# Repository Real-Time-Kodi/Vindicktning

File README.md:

# Vindicktning
This board is designed to fit within the case of the Ikea Vindriktning and
replicate its functionality while replacing the main MCU with an ESP8266 for
home automation use. It also adds multiple i2c headers for adding other air 
quality sensors.  

# Harvesting Components
This step is relatively straightforward, I recommend using a soldering 
hotplate and a pinecil or similar small, temperature controlled iron.
The first step is to harvest the parts you'll need from the Vindriktning
 board. Remove all of the components circled in red. The easiest way to do this
 is to scrape the LEDs off of the underside of the board and put it on the
hotplate, removing each component with tweezers once the board is good and hot.  
You'll need both of the connectors, the electrolytic cap, and the diode.

# Parts List
- [Usb Type C Connector](https://www.mouser.com/ProductDetail/640-USB4120-03-C)
- 7x 0805 0.1uf Capacitors
- 3x WS2812b LEDs
- 1x 0805 10k Resistor(optional for buzzer)
- 1x [MMBT2222](https://www.mouser.com/ProductDetail/241-MMBT2222AR100001) SOT Transistor or equivalent(optional for buzzer)
- 1x Standard buzzer(optional)
- Fine wire(Optional for USB data hookup)
- Wemos D1 Mini  

I have a few kits available on my [tindie page](https://www.tindie.com/products/realtimekodi/vindriktning-air-quality-sensor-mod-boardesphome/#shipping).  

# Board Assembly
Using your preferred method, solder each of the components on to their 
designated pads. All of the capacitors are 0.1uf except for the electrolytic 
capacitor. Mind the polarity on both the capacitor and the diode!

I recommend using the hotplate for all of the surface mount components and
verifying that you get 5v at this point before proceeding to the next steps.
Don't forget to solder the LEDs on the back.

The other board is easy to get wrong. Make sure the port and board are
facing the correct direction or the completed assembly will not fit into the
case! Look at the pictures to be sure of orientation. The ESP module on the 
Wemos D1 should fit into the board cutout and the USB port should be accessible.
Solder the boards together with small bits of wire or header pins.

It is easiest to solder the through-hole components before mating the boards 
together, this is the point where you should install the optional buzzer and 
any i2c headers you wish to use. The headers should have been included with the 
Wemos D1 and can be cut down to size with angle cutters.

# Mating the Boards
The board containing the Wemos D1 must be facing exactly as shown. Insert it 
into the slot and solder it on BOTH SIDES, making sure that it is exactly
perpendicular to the main PCB. Test the fitment before Reassembly!

# USB Data lines for External Programming(Optional)
There are two labeled test pads on the main PCB (D+ and D-) those two pads can
be connected to the corresponding D+ and D- pins on the Wemos D1's USB to Serial chip to allow
you to program the device without opening it up. There are several different USB -> Serial chips on the
D1. Check the diagram below for specific pinout. Many modules will have the model numbers sanded off of
the CH341. Note that this is not a valid implementation of USB and the type-c cable will only be able to 
program the device when inserted right-side up.

# Reassembly
The Vindrictning top case needs to have these 2 standoffs removed. Flush 
cutters work best.

The new board can then be installed with the screws that 
came with the vindriktning. Keep an eye on the header pins that hold the 
Wemos D1 to its pcb, they need to be trimmed as flush as possible in order for 
the board to clear the fan screws.

# Programming
See the included esphome example. It initializes all of the inbuilt perpherals 
and has a function for fading the LEDs between colors based on the c02, pm2.5, 
and VOC concentrations. Program it with whichever method you usually use to 
program ESPHome devices.  
Please remember that the usb port will only connect the data pins with the type-c 
connector in the upward orientation.  

# Adding I2C Sensors
Additional sensors can be added using the I2C headers. There are three of them of them
with the following pinout: SDA | SCL | GND | VCC  
The I2C4 header on the top of the board has positive and negative swapped so that it 
can be used with [this sensor](https://www.amazon.com/gp/product/B0BHHRT1F6/): 
SDA | SCL | VCC | GND  
The voltage is 3.3 by default but it can be set to 5v by cutting the voltage selector
trace and adding a solder blob on the 5v side. The silkscreen is clearly labled.

Check [ESPHome.io](https://esphome.io/) for supported sensors and configuration
documentation.

Sensors I have used:
- SCD40 (CO2)
- BME280 (Temperature Humiditity Pressure)
- BME680
- BMP280 (Temperature Pressure)
- CCS811 (eC02 Volatile Organic Compounds)

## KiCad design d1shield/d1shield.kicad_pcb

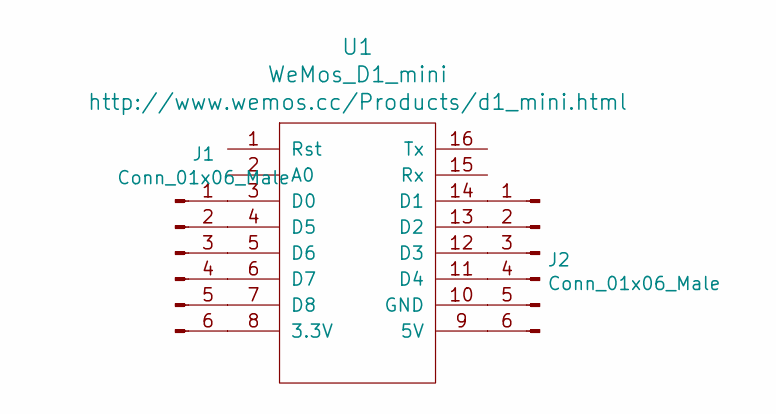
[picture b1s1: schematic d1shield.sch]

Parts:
J1, J2: Conn_01x06_Male; Edge
U1: WeMos_D1_mini; wemos-d1-mini-connectors-only

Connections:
unnamed: J1.1, U1.3 (D0)
unnamed: J1.2, U1.4 (D5)
unnamed: J1.3, U1.5 (D6)
unnamed: J1.4, U1.6 (D7)
unnamed: J1.5, U1.7 (D8)
unnamed: J1.6, U1.8 (3.3V)
unnamed: J2.1, U1.14 (D1)
unnamed: J2.2, U1.13 (D2)
unnamed: J2.3, U1.12 (D3)
unnamed: J2.4, U1.11 (D4)
unnamed: J2.5, U1.10 (GND)
unnamed: J2.6, U1.9 (5V)

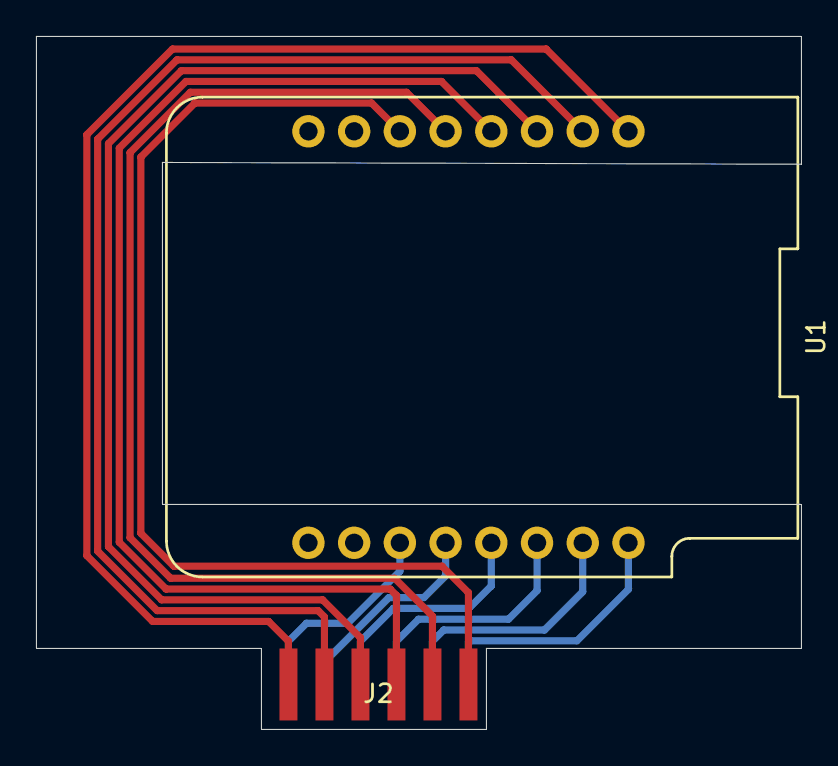
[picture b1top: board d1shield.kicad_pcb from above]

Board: 2 copper layers, 42.5 x 38.5 mm, 3 parts (1 on the bottom side), 12 nets.

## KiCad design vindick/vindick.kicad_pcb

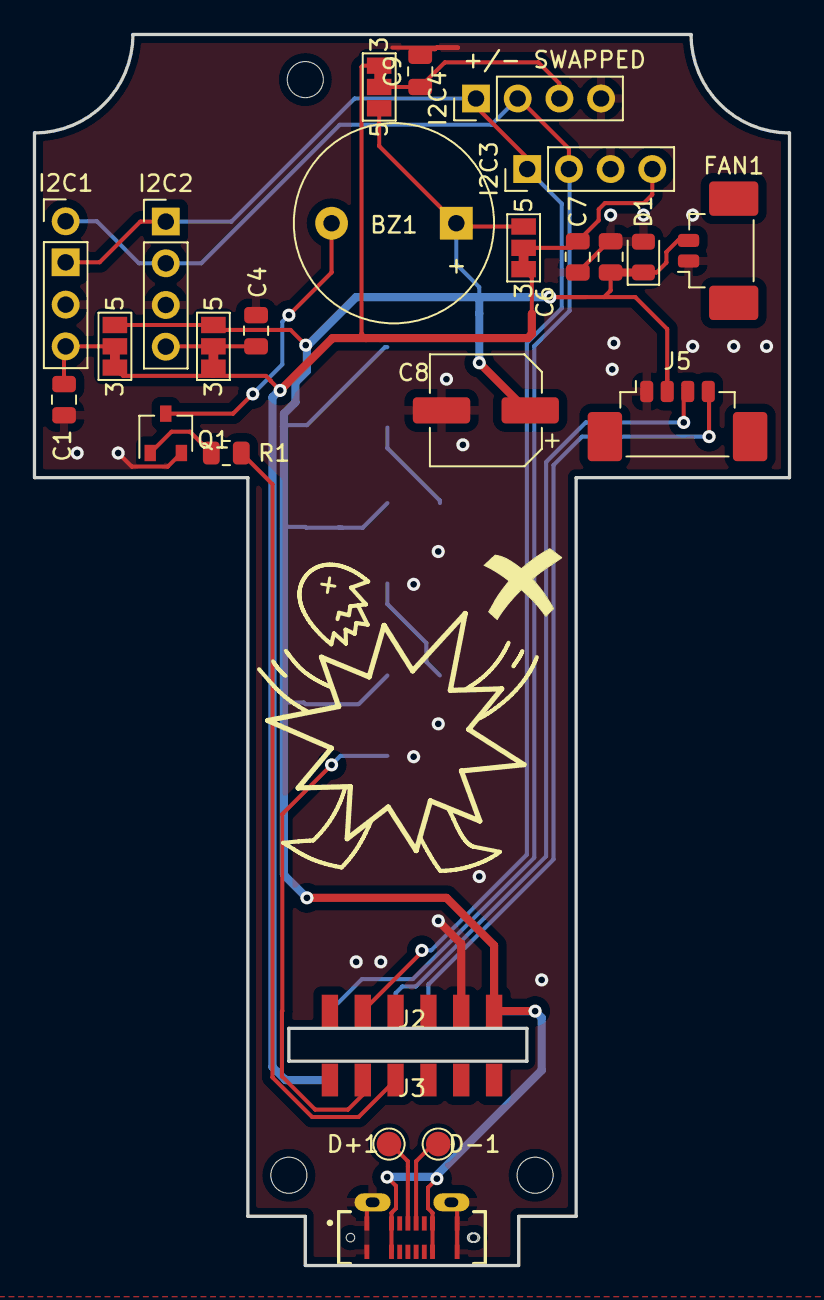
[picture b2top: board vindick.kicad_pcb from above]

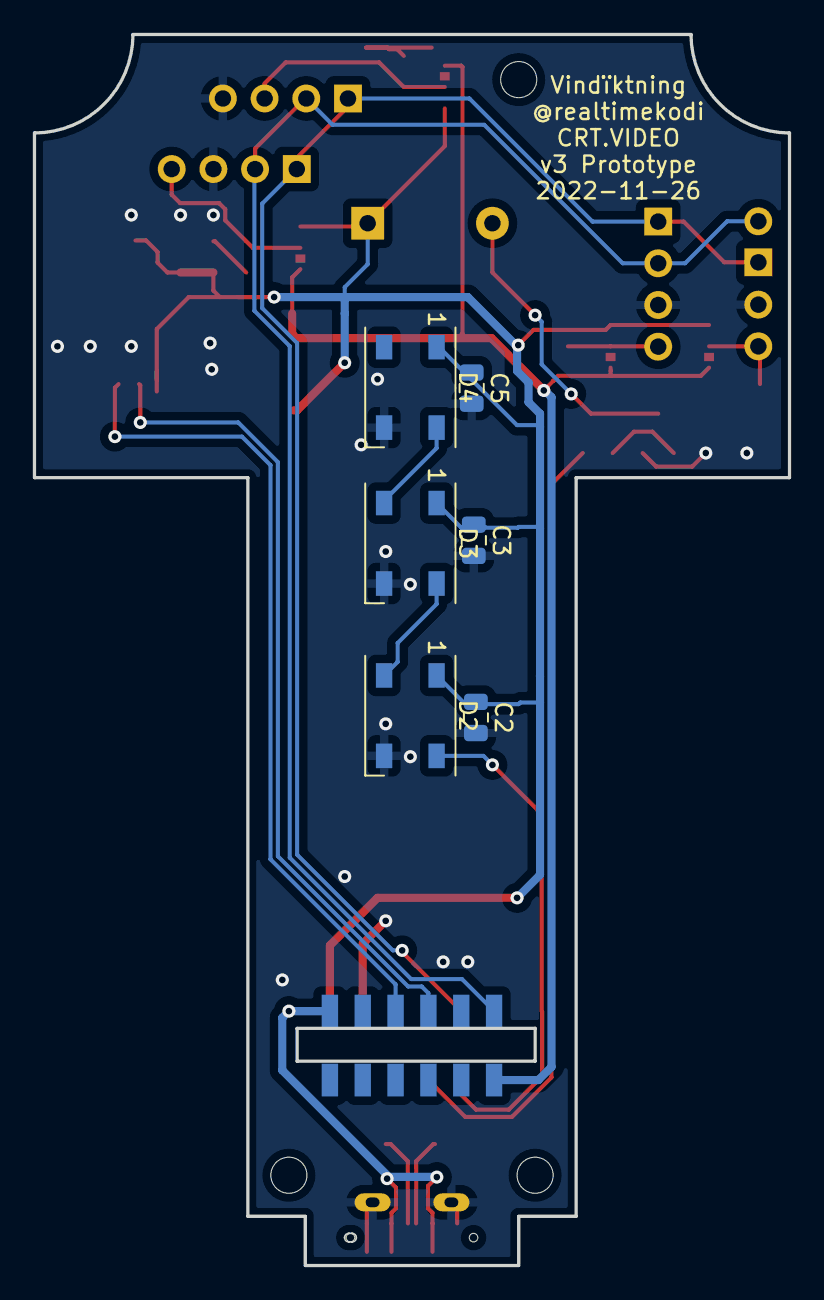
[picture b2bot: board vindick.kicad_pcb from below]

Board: 2 copper layers, 46.0 x 75.0 mm, 31 parts (6 on the bottom side), 19 nets.

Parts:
BZ1: Buzzer; Buzzer_12x9.5RM7.6
C1, C2, C3, C4, C5, C6, C7, C9: C; C_0805_2012Metric
C8: CP; CP_Elec_6.3x7.7
D1: D; D_0805_2012Metric
D2, D3, D4: WS2812B; LED_WS2812B_PLCC4_5.0x5.0mm_P3.2mm
D+1: D+; TestPoint_Pad_D1.5mm
D-1: D-; TestPoint_Pad_D1.5mm
FAN1: PicoBlade 2; Molex_PicoBlade_53398-0271_1x02-1MP_P1.25mm_Vertical
I2C1, I2C3, I2C4: Conn_01x04_Male; PinHeader_1x04_P2.54mm_Vertical
I2C2: I2C1; PinHeader_1x04_P2.54mm_Vertical
J1: USB4120-03-C_REVA; GCT_USB4120-03-C_REVA
J2: TopSide; Edgesmol
J3: USB Side; Edgesmol
J5: Conn_01x04_Male; Molex_PicoBlade_53398-0471_1x04-1MP_P1.25mm_Vertical
JP1, JP2, JP3, JP4: 3/5; SolderJumper-3_P1.3mm_Bridged12_Pad1.0x1.5mm_NumberLabels
Q1: Q_NPN_BEC; SOT-23W
R1: R; R_0805_2012Metric

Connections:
+3V3: J3.6, JP1.1 (A), JP2.1 (A), JP3.1 (A), JP4.1 (A)
/BUZZ: J3.4, R1.2
/D+: D+1.1, J1.A6 (D1+), J1.B6 (D2+)
/D-: D-1.1, J1.A7 (D1-), J1.B7 (D2-)
/LIGHT: D2.4 (DIN), J3.5
/RXD: J2.4, J5.3
/SCL: I2C1.2, I2C2.2, I2C3.2, I2C4.2, J2.6
/SDA: I2C1.1, I2C2.1, I2C3.1, I2C4.1, J2.5
/TXD: J2.3, J5.4
GND: C1.2, C2.2, C3.2, C4.2, C5.2, C6.2, C7.2, C8.2, C9.2, D1.2 (A), D2.3 (VSS), D3.3 (VSS), D4.3 (VSS), FAN1.1, I2C1.3, I2C2.3, I2C3.3, I2C4.3, J1.A1 (GND_A), J1.A12 (GND_A), J1.B1 (GND_B), J1.B12 (GND_B), J1.S1 (SHIELD), J1.S3 (SHIELD), J2.2, J5.1, Q1.2 (E)
unnamed: BZ1.2 (+), Q1.3 (C)
unnamed: C1.1, I2C1.4, JP1.2 (C)
unnamed: C4.1, I2C2.4, JP2.2 (C)
unnamed: C6.1, I2C3.4, JP3.2 (C)
unnamed: C9.1, I2C4.4, JP4.2 (C)
unnamed: D2.2 (DOUT), D3.4 (DIN)
unnamed: D3.2 (DOUT), D4.4 (DIN)
unnamed: Q1.1 (B), R1.1
VBUS: BZ1.1 (-), C2.1, C3.1, C5.1, C7.1, C8.1, D1.1 (K), D2.1 (VDD), D3.1 (VDD), D4.1 (VDD), FAN1.2, J1.A4 (VBUS_A), J1.A9 (VBUS_A), J1.B4 (VBUS_B), J1.B9 (VBUS_B), J2.1, J5.2, JP1.3 (B), JP2.3 (B), JP3.3 (B), JP4.3 (B)

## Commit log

2023-02-27 Initial PCB Commit
2023-02-27 Cleanup
2023-02-27 Added esphome example
2023-02-27 Readme Update
2023-02-27 pictures
2023-02-27 Add Parts List
2023-03-04 Clarity
2023-03-05 Added homeassistant snapshot
2023-03-12 Comments
2023-03-13 Added more config examples
2024-01-17 Fixed pm2.5 sensor startup behaviour
2024-02-25 Added gerbers since the shop is gone
